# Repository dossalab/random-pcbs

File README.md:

# My collection of random PCBs (printed-circuit-boards)

These things are too minor to create separate repositories for them.

## What's included

Name | Description | Notes
-----|-------------|------
ips-display-breakout | Breakout for ST7789-based 240x240 IPS display from Aliexpress |
library | Directory containing common footprints & libraries |
nrf-card | Development board in a size of a credit card containing NRF52832, SD card breakout, ST7789-based display and more | This was done before I discovered that NRF52 consumes 32 uA of current, so it has external RTC and unnecessary powerup logic.
sd-card-debug | SD/MMC card breakout board intended for JTAG debugging on Rockchip / Alwinner boards | Codename "dildo" - never ordered

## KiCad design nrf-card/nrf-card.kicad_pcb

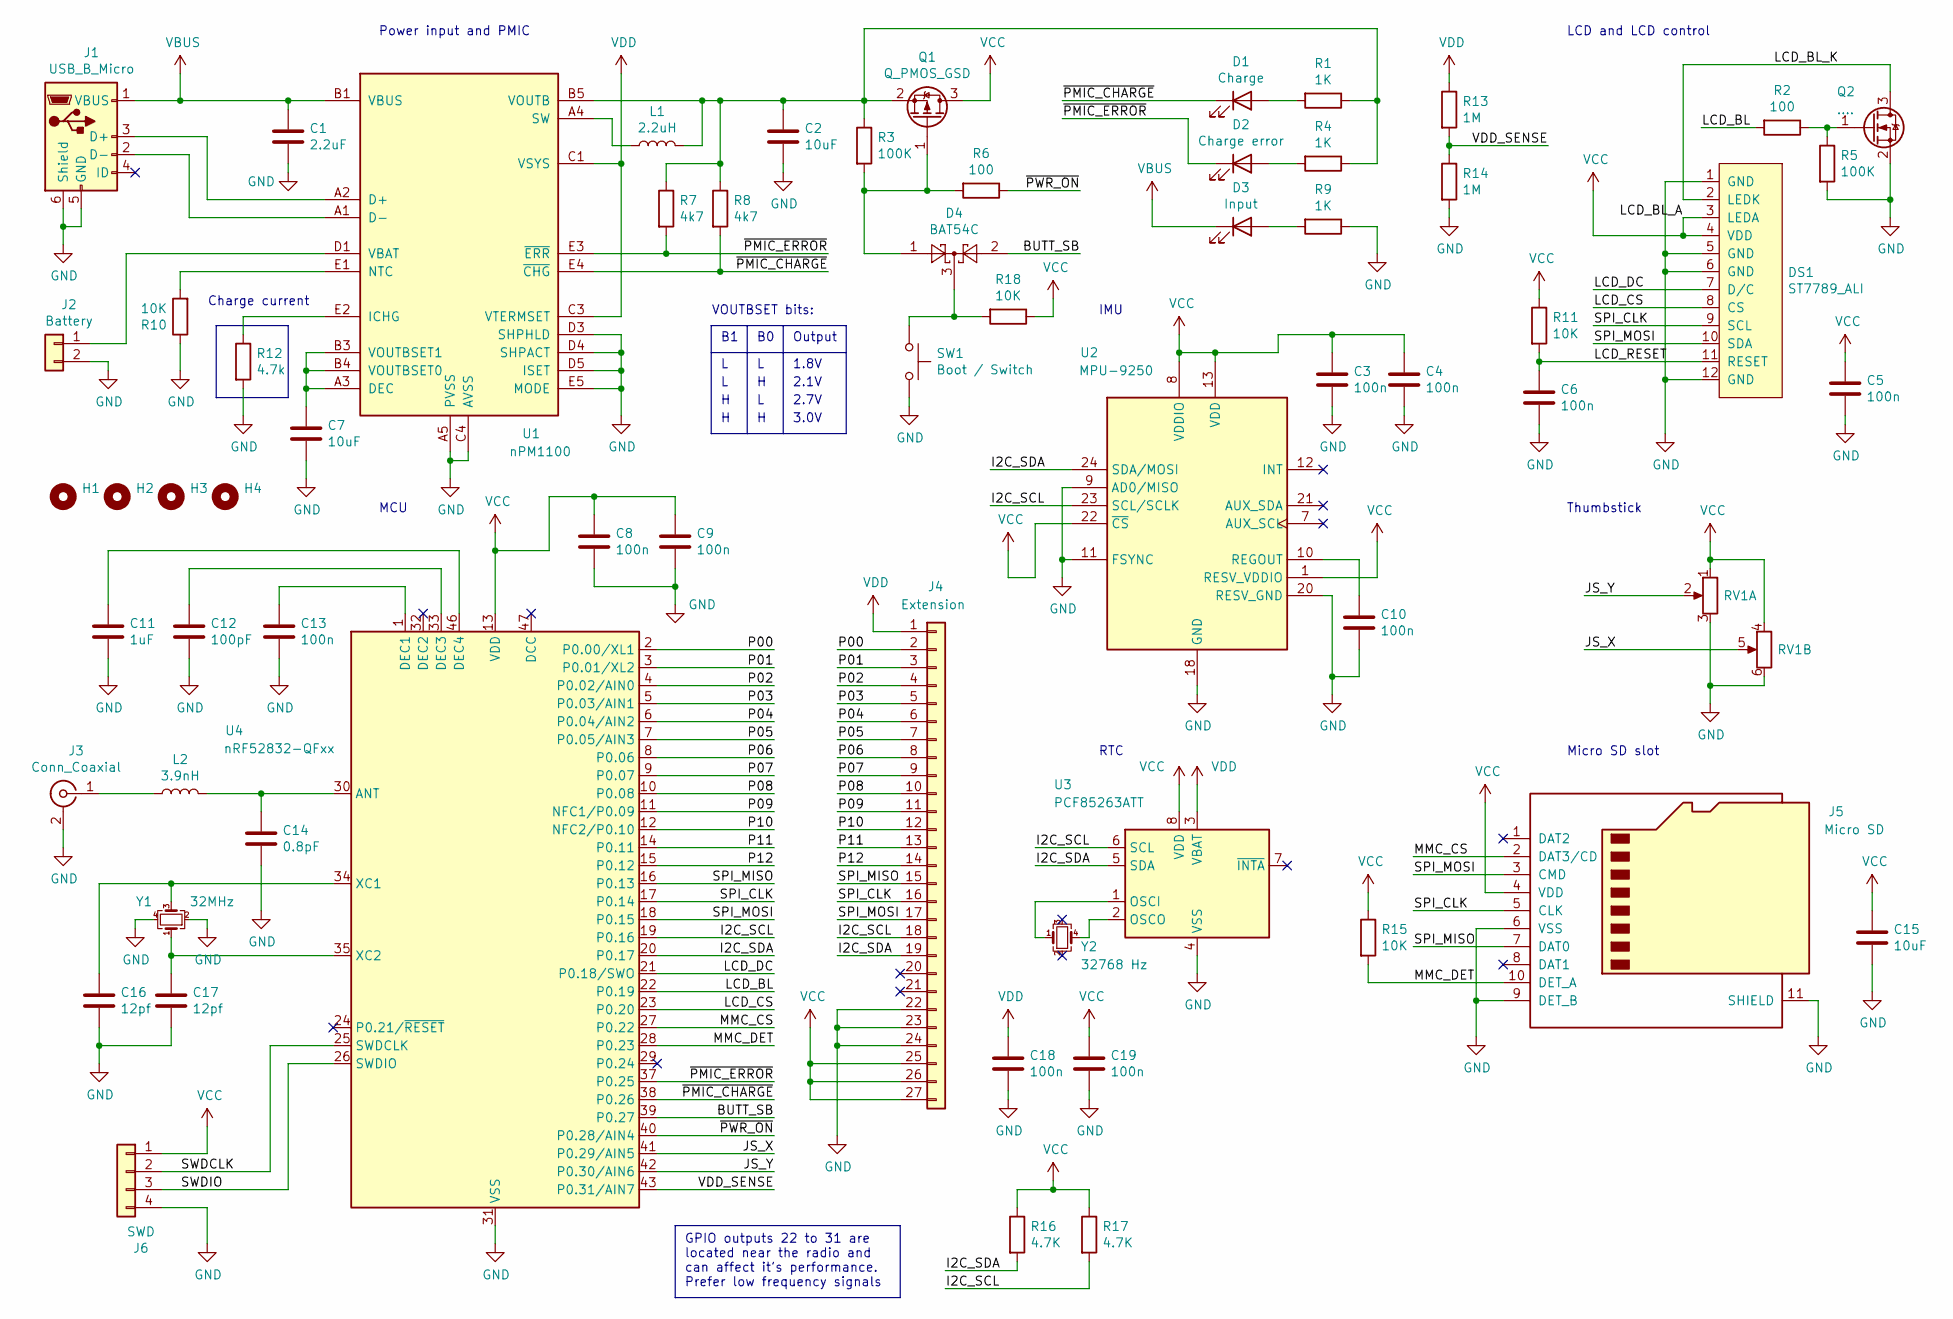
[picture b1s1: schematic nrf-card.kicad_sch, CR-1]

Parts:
C1: 2.2uF; C_0603_1608Metric
C2, C7, C15: 10uF; C_0603_1608Metric
C3, C4, C5, C6, C8, C9, C10, C13, C18, C19: 100n; C_0603_1608Metric
C11: 1uF; C_0603_1608Metric
C12: 100pF; C_0603_1608Metric
C14: 0.8pF; C_0603_1608Metric
C16, C17: 12pf; C_0603_1608Metric
D1: Charge; LED_0603_1608Metric
D2: Charge error; LED_0603_1608Metric
D3: Input; LED_0603_1608Metric
D4: BAT54C; SOT-23
DS1: ST7789_ALI
H1, H2, H3, H4: Mounting hole; MountingHole_3.2mm_M3_ISO7380
J1: USB_B_Micro; USB_Micro-B_Wuerth_629105150521
J2: Battery; JST_PH_S2B-PH-K_1x02_P2.00mm_Horizontal
J3: Conn_Coaxial; U.FL_Hirose_U.FL-R-SMT-1_Vertical
J4: Extension; PinHeader_1x27_P2.54mm_Vertical
J5: Micro SD; microSD_HC_Molex_104031-0811
J6: SWD; PinHeader_1x04_P2.54mm_Vertical
L1: 2.2uH; L_0805_2012Metric
L2: 3.9nH; L_0603_1608Metric
Q1: Q_PMOS_GSD; SOT-23
Q2: ....; SOT-23
R1, R4, R9: 1K; R_0603_1608Metric
R2, R6: 100; R_0603_1608Metric
R3, R5: 100K; R_0603_1608Metric
R7, R8: 4k7; R_0603_1608Metric
R10, R11, R15, R18: 10K; R_0603_1608Metric
R12: 4.7k; R_0603_1608Metric
R13, R14: 1M; R_0603_1608Metric
R16, R17: 4.7K; R_0603_1608Metric
RV1: Thumbstick; mini-thumbstick
SW1: Boot / Switch; SW_SPST_PTS645
U1: nPM1100; ST_WLCSP-25_Die444
U2: MPU-9250; InvenSense_QFN-24_3x3mm_P0.4mm
U3: PCF85263ATT; TSSOP-8_3x3mm_P0.65mm
U4: nRF52832-QFxx; QFN-48-1EP_6x6mm_P0.4mm_EP4.6x4.6mm
Y1: 32MHz; Crystal_SMD_EuroQuartz_X22-4Pin_2.5x2.0mm
Y2: 32768 Hz; Crystal_SMD_SeikoEpson_MC146-4Pin_6.7x1.5mm

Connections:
/BUTT_SB: D4.2, U4.39 (P0.27)
/I2C_SCL: J4.18, R17.2, U2.23 (SCL/SCLK), U3.6 (SCL), U4.19 (P0.16)
/I2C_SDA: J4.19, R16.2, U2.24 (SDA/MOSI), U3.5 (SDA), U4.20 (P0.17)
/JS_X: RV1.5, U4.41 (P0.29/AIN5)
/JS_Y: RV1.2, U4.42 (P0.30/AIN6)
/LCD_BL: R2.2, U4.22 (P0.19)
/LCD_BL_K: DS1.2 (LEDK), Q2.3 (D)
/LCD_CS: DS1.8 (CS), U4.23 (P0.20)
/LCD_DC: DS1.7 (D/C), U4.21 (P0.18/SWO)
/LCD_RESET: C6.1, DS1.11 (RESET), R11.2
/MMC_CS: J5.2 (DAT3/CD), U4.27 (P0.22)
/MMC_DET: J5.10 (DET_A), R15.2, U4.28 (P0.23)
/P00: J4.2, U4.2 (P0.00/XL1)
/P01: J4.3, U4.3 (P0.01/XL2)
/P02: J4.4, U4.4 (P0.02/AIN0)
/P03: J4.5, U4.5 (P0.03/AIN1)
/P04: J4.6, U4.6 (P0.04/AIN2)
/P05: J4.7, U4.7 (P0.05/AIN3)
/P06: J4.8, U4.8 (P0.06)
/P07: J4.9, U4.9 (P0.07)
/P08: J4.10, U4.10 (P0.08)
/P09: J4.11, U4.11 (NFC1/P0.09)
/P10: J4.12, U4.12 (NFC2/P0.10)
/P11: J4.13, U4.14 (P0.11)
/P12: J4.14, U4.15 (P0.12)
/SPI_CLK: DS1.9 (SCL), J4.16, J5.5 (CLK), U4.17 (P0.14)
/SPI_MISO: J4.15, J5.7 (DAT0), U4.16 (P0.13)
/SPI_MOSI: DS1.10 (SDA), J4.17, J5.3 (CMD), U4.18 (P0.15)
/SWDCLK: J6.2, U4.25 (SWDCLK)
/SWDIO: J6.3, U4.26 (SWDIO)
/VDD_SENSE: R13.2, R14.1, U4.43 (P0.31/AIN7)
/~PMIC_CHARGE: D1.1 (K), R8.2, U1.E4 (~CHG), U4.38 (P0.26)
/~PMIC_ERROR: D2.1 (K), R7.2, U1.E3 (~ERR), U4.37 (P0.25)
/~PWR_ON: R6.1, U4.40 (P0.28/AIN4)
GND: C1.2, C2.2, C3.2, C4.2, C5.2, C6.2, C7.2, C8.2, C9.2, C10.2, C11.2, C12.2, C13.2, C14.2, C15.2, C16.2, C17.2, C18.2, C19.2, DS1.1 (GND), DS1.5 (GND), DS1.6 (GND), DS1.12 (GND), J1.5 (GND), J1.6 (Shield), J2.2, J3.2 (Ext), J4.22, J4.23, J4.24, J5.6 (VSS), J5.9 (DET_B), J5.11 (SHIELD), J6.4, Q2.2 (S), R5.2, R9.1, R10.1, R12.2, R14.2, RV1.3, RV1.6, SW1.2, U1.A5 (PVSS), U1.C4 (AVSS), U1.C5 (AVSS), U1.D3 (SHPHLD), U1.D4 (SHPACT), U1.D5 (ISET), U1.E5 (MODE), U2.9 (AD0/MISO), U2.11 (FSYNC), U2.18 (GND), U2.20 (RESV_GND), U3.4 (VSS), U4.31 (VSS), U4.45 (VSS), U4.49 (VSS), Y1.2, Y1.4
unnamed: D1.2 (A), R1.2
unnamed: D2.2 (A), R4.2
unnamed: D3.2 (A), R9.2
unnamed: D4.3, R18.2, SW1.1
unnamed: J1.3 (D+), U1.A2 (D+)
unnamed: J1.2 (D-), U1.A1 (D-)
unnamed: J3.1 (In), L2.1
unnamed: D4.1, Q1.1 (G), R3.2, R6.2
unnamed: C2.1, L1.2, Q1.2 (S), R1.1, R3.1, R4.1, R7.1, R8.1, U1.B5 (VOUTB)
unnamed: Q2.1 (G), R2.1, R5.1
unnamed: C7.1, U1.A3 (DEC), U1.B3 (VOUTBSET1), U1.B4 (VOUTBSET0)
unnamed: R12.1, U1.E2 (ICHG)
unnamed: R10.2, U1.E1 (NTC)
unnamed: L1.1, U1.A4 (SW)
unnamed: C10.1, U2.10 (REGOUT)
unnamed: U3.1 (OSCI), Y2.1
unnamed: U3.2 (OSCO), Y2.4
unnamed: C14.1, L2.2, U4.30 (ANT)
unnamed: C13.1, U4.1 (DEC1)
unnamed: C12.1, U4.33 (DEC3)
unnamed: C11.1, U4.46 (DEC4)
unnamed: C16.1, U4.34 (XC1), Y1.3
unnamed: C17.1, U4.35 (XC2), Y1.1
VBAT: J2.1, U1.D1 (VBAT), U1.D2 (VBAT)
VBUS: C1.1, D3.1 (K), J1.1 (VBUS), U1.B1 (VBUS), U1.B2 (VBUS)
VCC: C3.1, C4.1, C5.1, C8.1, C9.1, C15.1, C19.1, DS1.3 (LEDA), DS1.4 (VDD), J4.25, J4.26, J4.27, J5.4 (VDD), J6.1, Q1.3 (D), R11.1, R15.1, R16.1, R17.1, R18.1, RV1.1, RV1.4, U2.1 (RESV_VDDIO), U2.8 (VDDIO), U2.13 (VDD), U2.22 (~CS), U3.8 (VDD), U4.13 (VDD), U4.36 (VDD), U4.48 (VDD)
VDD: C18.1, J4.1, R13.1, U1.C1 (VSYS), U1.C2 (VSYS), U1.C3 (VTERMSET), U3.3 (VBAT)

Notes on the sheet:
Micro SD slot
Power input and PMIC
IMU
GPIO outputs 22 to 31 are located near the radio and can affect it's performance. Prefer low frequency signals
2.7V
3.0V
RTC
VOUTBSET bits:
MCU
LCD and LCD control
2.1V
1.8V
Output
Charge current
Thumbstick

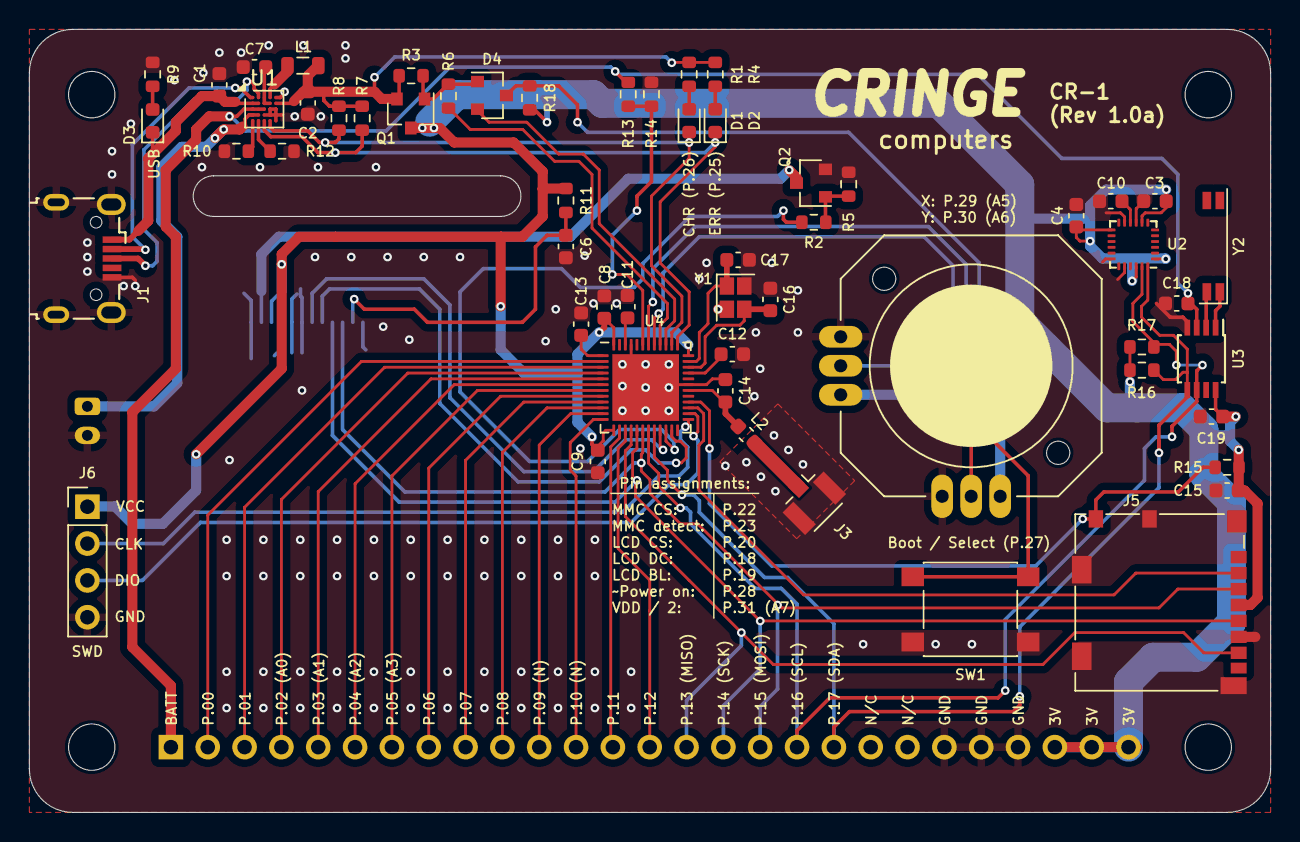
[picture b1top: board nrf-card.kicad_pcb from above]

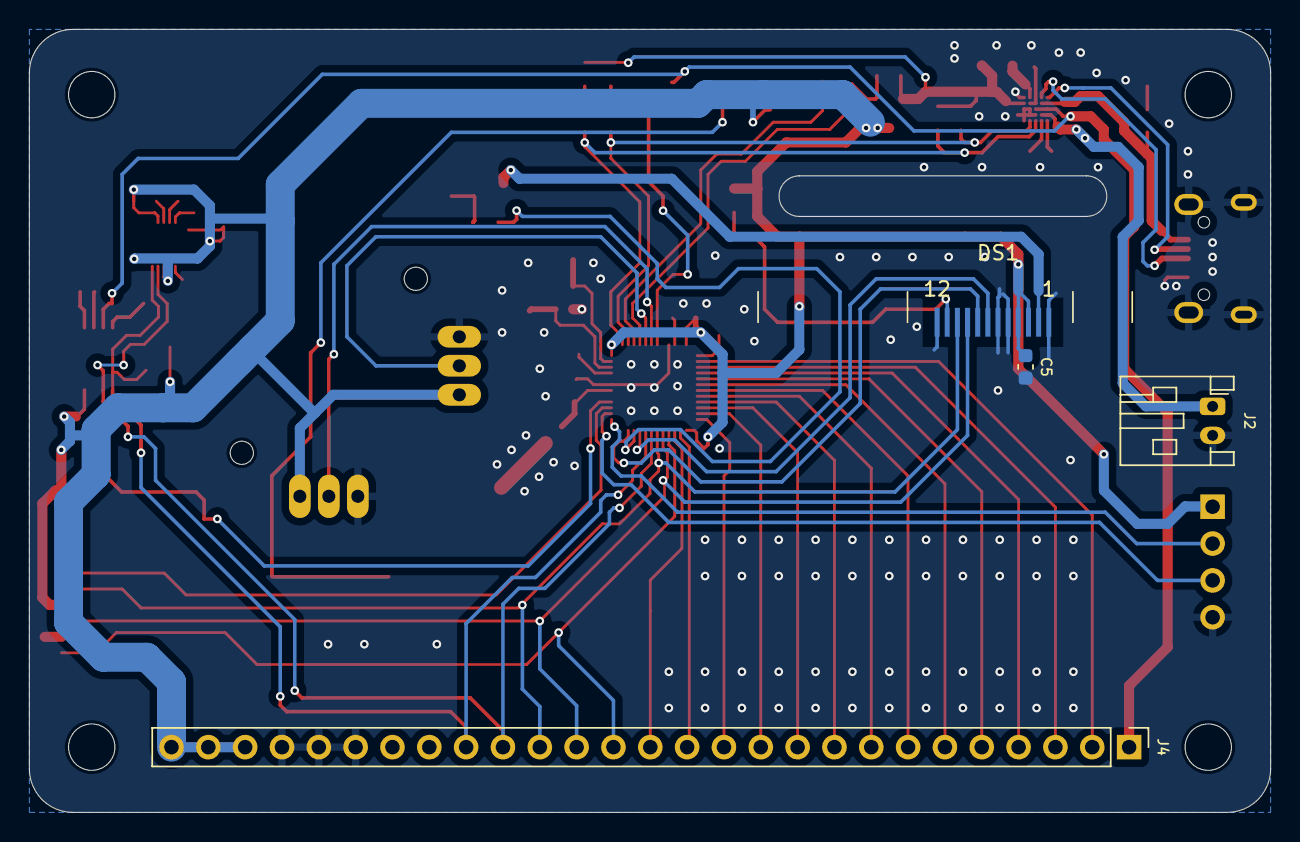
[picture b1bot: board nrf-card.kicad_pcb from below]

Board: 2 copper layers, 85.6 x 54.0 mm, 64 parts (4 on the bottom side), 62 nets.

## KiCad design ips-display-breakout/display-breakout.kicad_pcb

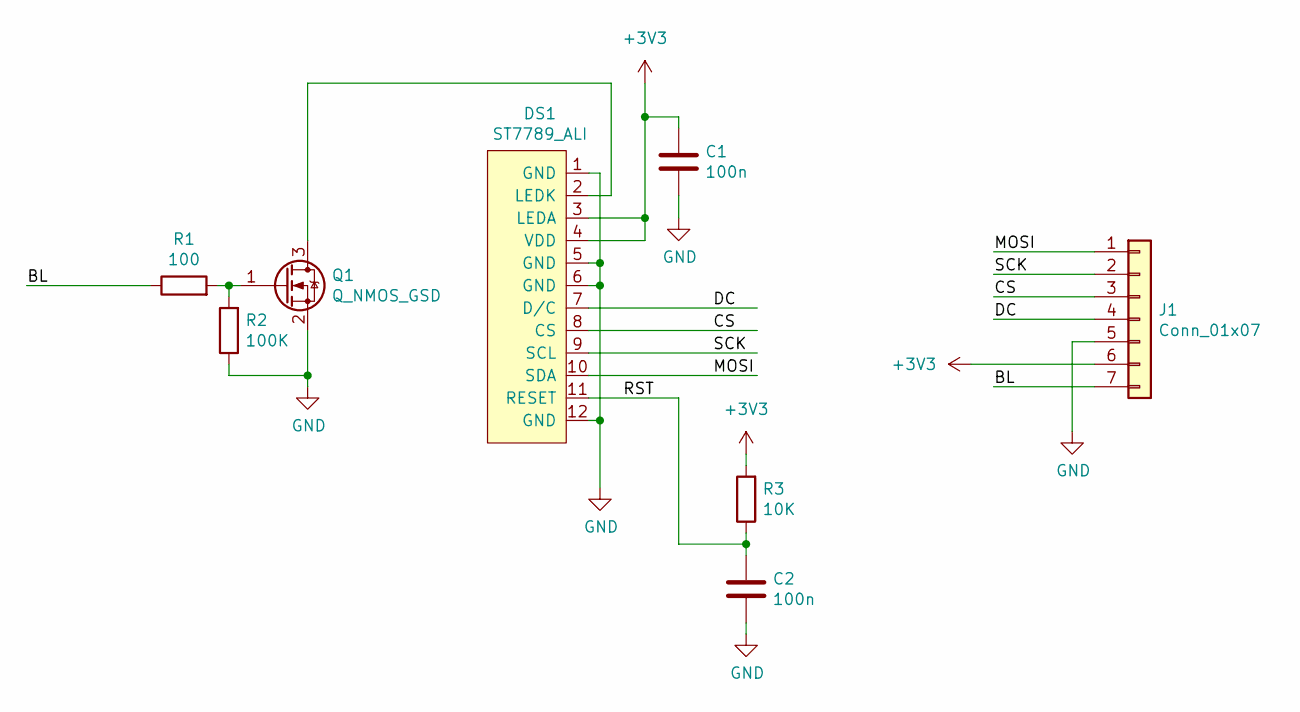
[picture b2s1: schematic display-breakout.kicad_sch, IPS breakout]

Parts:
C1, C2: 100n; C_0603_1608Metric
DS1: ST7789_ALI
J1: Conn_01x07; PinHeader_1x07_P2.54mm_Vertical
Q1: Q_NMOS_GSD; SOT-23
R1: 100; R_0603_1608Metric
R2: 100K; R_0603_1608Metric
R3: 10K; R_0603_1608Metric

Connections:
+3V3: C1.1, DS1.3 (LEDA), DS1.4 (VDD), J1.6, R3.2
/BL: J1.7, R1.1
/CS: DS1.8 (CS), J1.3
/DC: DS1.7 (D/C), J1.4
/MOSI: DS1.10 (SDA), J1.1
/RST: C2.1, DS1.11 (RESET), R3.1
/SCK: DS1.9 (SCL), J1.2
GND: C1.2, C2.2, DS1.1 (GND), DS1.5 (GND), DS1.6 (GND), DS1.12 (GND), J1.5, Q1.2 (S), R2.1
unnamed: DS1.2 (LEDK), Q1.3 (D)
unnamed: Q1.1 (G), R1.2, R2.2

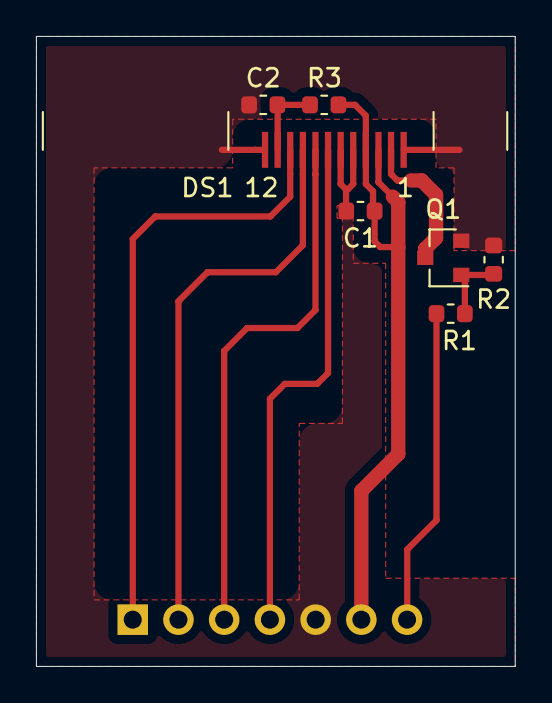
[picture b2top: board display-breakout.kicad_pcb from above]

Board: 2 copper layers, 26.6 x 35.0 mm, 8 parts (1 on the bottom side), 10 nets.

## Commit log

2025-07-26 ble receiver deserves a separate repository :)
